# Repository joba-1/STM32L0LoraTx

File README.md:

# STM32L0LoraTx

Firmware and PCB for a device that sends data with a STM32L0/RFM95, battery or solar powered, to a [LoraGW ESP8266/RFM95 node](https://github.com/joba-1/LoraGw)

## Build

* Download and install STM32CubeIDE (as of now version 1.5.1)
* Import this repo
* Open .ioc file and select "Project/Generate Code" (should download needed "firmware" files for the chip from ST)
* Build Release or Debug

## Wiring

connect Gnd of all components

### STM32L011

Not checked without, but generally recommended to use a small ceramic (~10nF) and big electrolyt condensator (~10µF) between + and - near STM pins

* Look at the ioc file with CubeMX pinout view.
* Vdd _and_ Vdda to 1.8-3.3V
* Vss to Gnd
* Boot0 pulled to Gnd (~10k) to safely boot from flash
* STLink for flashing and debug: SWD, SWC, Gnd, NRst (also can provide Vdd via JP1 and STLink-Rx to L0-Tx for serial out)

### BME280

* SDA=MOSI, SDC=MISO, others should be obvious

### RFM95W

* Ant=~8cm wire (vary length and position to get best average RSSI as reported by LoraRx). 
* NSS=CS, others should be obvious

### Serial

Rx of a usb to serial converter sends at 115200. I use this command (serial port name ttyUSB_ser_red is defined in my /etc/udev/rules.d)
    pio device monitor -p /dev/ttyUSB_ser_red -b 115200

### LED

can be used without resistor. I use 1kOhm to save battery

## References

Good resource for STM32 is [Stefan Frings](http://stefanfrings.de/stm32/stm32l0.html)
He has links to reference, datasheet, errata and more. E.g.:

* [STM32L011 Datasheet](https://www.st.com/resource/en/datasheet/stm32l011d3.pdf)
* [STM32L011 Reference](https://www.st.com/resource/en/reference_manual/dm00108282-ultra-low-power-stm32l0x1-advanced-arm-based-32-bit-mcus-stmicroelectronics.pdf)
* [STM32L011 Errata](https://www.st.com/resource/en/errata_sheet/dm00237371-stm32l011x3-4-device-limitations-stmicroelectronics.pdf)
* [Power consumption](http://www.st.com/content/ccc/resource/technical/document/application_note/27/58/8e/81/79/fb/4f/ac/DM00108286.pdf/files/DM00108286.pdf/jcr:content/translations/en.DM00108286.pdf)

## Power Info Bits

* Examples for LL are here: STM32Cube/Repository/STM32Cube_FW_L0_V1.11.2/Projects/NUCLEO-L073RZ/Examples_LL/RTC/RTC_ExitStandbyWithWakeUpTimer
* Periodic wakeup timer is in Reference 22.4.6 (Periodic auto-wakeup)
* 1s to 18h periodic wakeup with ck_spre = 1s (see 22.4.3) and WUCKSEL [2:1] = 10
* Enable by WUTE bit in RTC_CR register
* Once setup it runs in normal and low power. 
* Sets WUTF flag in RTC_ISR if elapsed and reloads RTC_WUTR (timer counter). User resets WUTF
* Set WUTIE bit in RTC_CR to generate interrupt to wake up from low power modes
* System reset and Sleep, Stop, Standby have no influence on the WUT (wakeup timer)
* Save Lora frame counter in backup register: Reference 22.7.20 RTC backup registers (RTC_BKPxR)
* I couldnt make it work with LL lib, had to use big fat HAL for RCC and RTC. What is missing?

        LL_RTC_DisableWriteProtection(RTC);
        LL_RTC_WAKEUP_Disable(RTC);
        while( !LL_RTC_IsActiveFlag_WUTW(RTC) );
        LL_RTC_WAKEUP_SetClock(RTC, LL_RTC_WAKEUPCLOCK_CKSPRE);
        LL_RTC_WAKEUP_SetAutoReload(RTC, 3); // wake up every 3+1 s
        LL_RTC_EnableIT_WUT(RTC);
        LL_RTC_WAKEUP_Enable(RTC);
        LL_RTC_EnableWriteProtection(RTC);
        while( LL_RTC_IsActiveFlag_WUTW(RTC) );
        LL_RTC_ClearFlag_WUT(RTC);
        NVIC_ClearPendingIRQ(RTC_IRQn);

## Status

Working and sending LoRa packets to my LoraGW ESP8266 gateway (battery voltages and bme280 weather data)

Two devices operating with 2 AA 1.5V batteries (so far using 0.2-0.4 V per year, so >5 years between battery swaps is more than realistic).
They send battery voltage data from within a car trunc - not ideal for RF :) - to a nearby house with no signal problems.

One device runs "forever" with a 3.7 Lipo ~1.6Ah, a ~3x8 cm² 5V solar cell and a small solar charger board (reducing vcc out a bit with a diode). No capacity problems during winter.

## Todo

* Provide more sensor data (probably more ADC stuff and more generic)
* Move GPIO pins (CS, LED) to non-ADC pins to have them available for voltage measurements

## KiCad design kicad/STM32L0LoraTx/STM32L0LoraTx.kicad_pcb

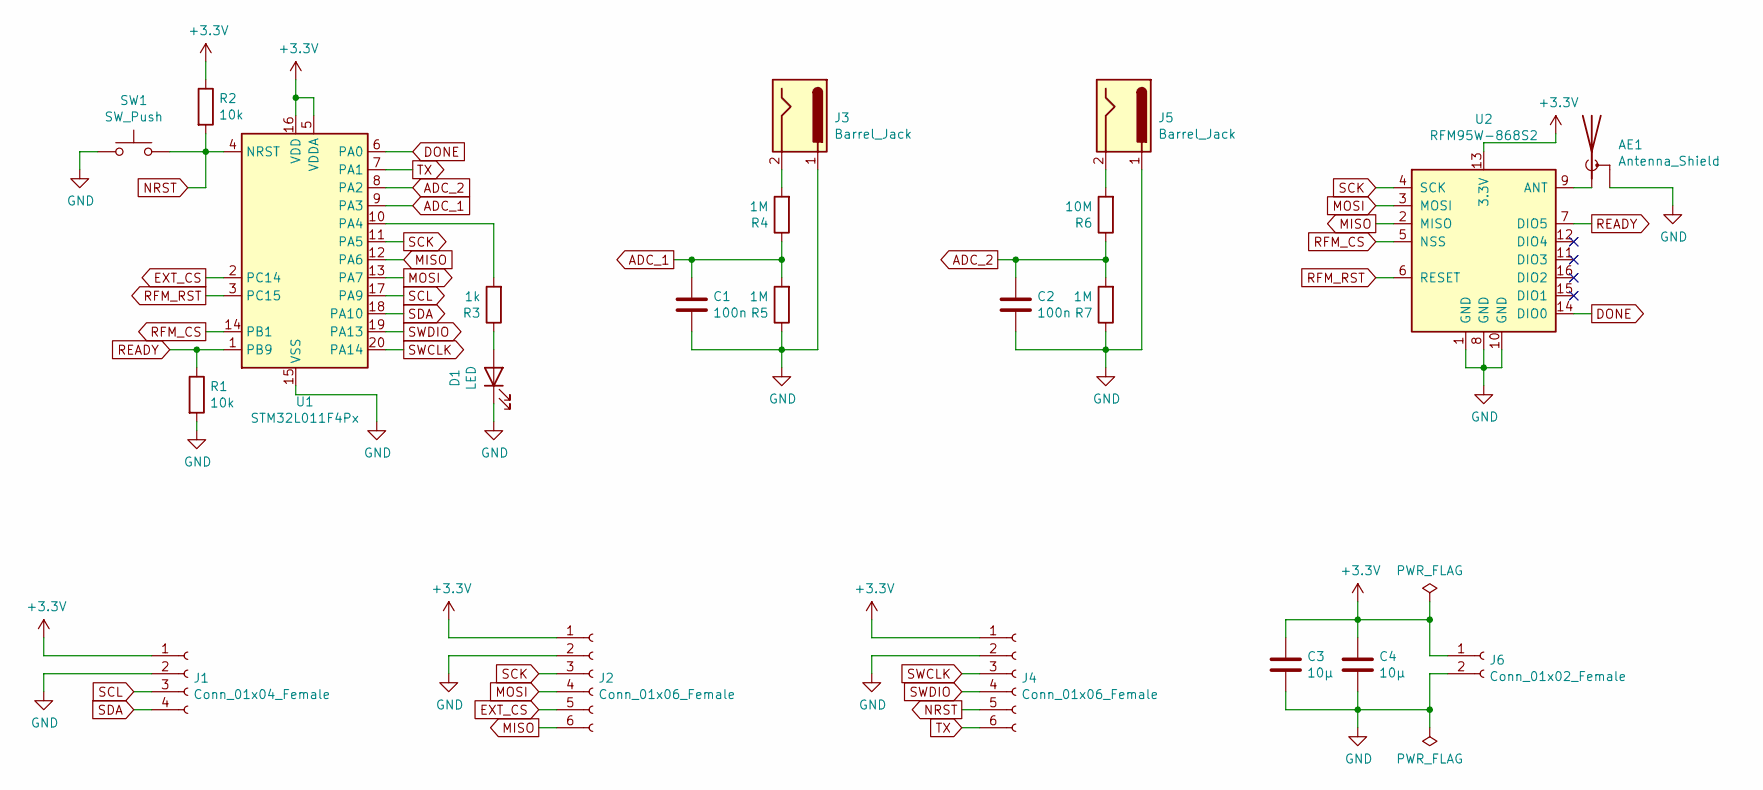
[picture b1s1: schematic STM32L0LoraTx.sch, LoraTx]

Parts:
AE1: Antenna_Shield; Molex_Microcoaxial_RF
C1, C2: 100n; C_0805_HandSoldering
C3, C4: 10µ; C_0805_HandSoldering
D1: LED; LED_0805_HandSoldering
J1: Conn_01x04_Female; JST_EH_B04B-EH-A_04x2.50mm_Straight
J2, J4: Conn_01x06_Female; JST_EH_B06B-EH-A_06x2.50mm_Straight
J3, J5: Barrel_Jack; TerminalBlock_Altech_AK300-2_P5.00mm
J6: Conn_01x02_Female; JST_EH_B02B-EH-A_02x2.50mm_Straight
R1, R2: 10k; R_0805_HandSoldering
R3: 1k; R_0805_HandSoldering
R4, R5, R7: 1M; R_0805_HandSoldering
R6: 10M; R_0805_HandSoldering
SW1: SW_Push; SW_PUSH_6mm_h5mm
U1: STM32L011F4Px; TSSOP-20_4.4x6.5mm_Pitch0.65mm
U2: RFM95W-868S2; Hopref_RFM9XW_SMD

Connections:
+3V3: C3.1, C4.1, J1.1, J2.1, J4.1, J6.1, R2.1, U1.5 (VDDA), U1.16 (VDD), U2.13 (3.3V)
ADC_1: C1.1, R4.1, R5.2, U1.9 (PA3)
ADC_2: C2.1, R6.1, R7.2, U1.8 (PA2)
DONE: U1.6 (PA0), U2.14 (DIO0)
EXT_CS: J2.5, U1.2 (PC14)
GND: AE1.2 (Shield), C1.2, C2.2, C3.2, C4.2, D1.1 (K), J1.2, J2.2, J3.1, J4.2, J5.1, J6.2, R1.2, R5.1, R7.1, SW1.1, U1.15 (VSS), U2.1 (GND), U2.8 (GND), U2.10 (GND); also elsewhere on the board
MISO: J2.6, U1.12 (PA6), U2.2 (MISO)
MOSI: J2.4, U1.13 (PA7), U2.3 (MOSI)
NRST: J4.5, R2.2, SW1.2, U1.4 (NRST); also elsewhere on the board
unnamed: AE1.1 (A), U2.9 (ANT)
unnamed: D1.2 (A), R3.1
unnamed: J3.2, R4.2
unnamed: J5.2, R6.2
unnamed: R3.2, U1.10 (PA4)
READY: R1.1, U1.1 (PB9), U2.7 (DIO5)
RFM_CS: U1.14 (PB1), U2.5 (NSS)
RFM_RST: U1.3 (PC15), U2.6 (RESET)
SCK: J2.3, U1.11 (PA5), U2.4 (SCK)
SCL: J1.3, U1.17 (PA9)
SDA: J1.4, U1.18 (PA10)
SWCLK: J4.3, U1.20 (PA14)
SWDIO: J4.4, U1.19 (PA13)
TX: J4.6, U1.7 (PA1)

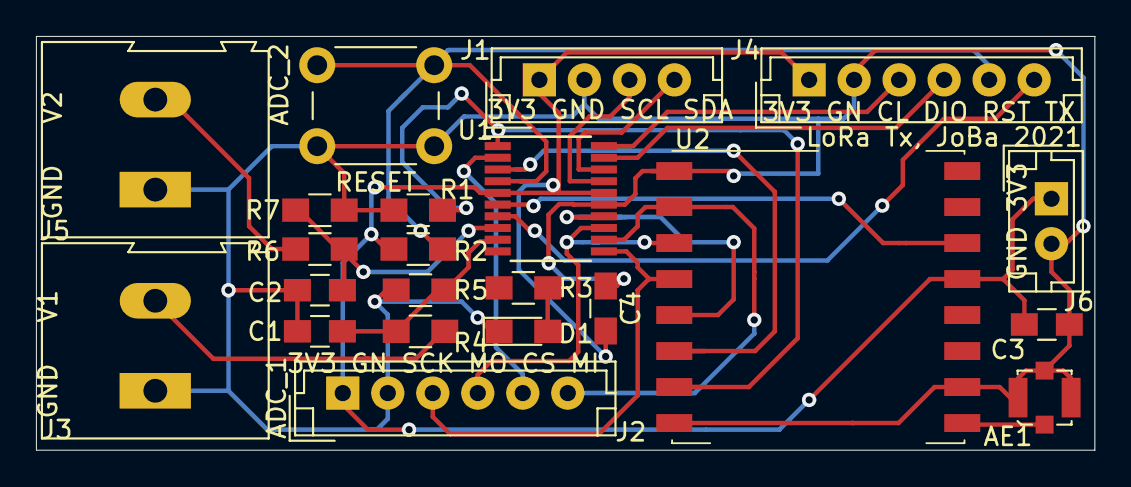
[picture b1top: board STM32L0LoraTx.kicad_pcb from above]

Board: 2 copper layers, 58.8 x 23.0 mm, 22 parts (0 on the bottom side), 23 nets.

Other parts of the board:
RESET: SW_Push; SW_PUSH_6mm_h5mm

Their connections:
GND: RESET.1; also elsewhere on the board
NRST: RESET.2; also elsewhere on the board

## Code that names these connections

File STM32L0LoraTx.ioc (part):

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PA0-CK_IN.GPIO_Label=RFM_D0
PA0-CK_IN.GPIOParameters=GPIO_Label
PA6.Mode=Full_Duplex_Master
PA7.Mode=Full_Duplex_Master
PA10.Mode=I2C
Mcu.UserName=STM32L011F4Px
PB9-BOOT0.GPIO_Label=RFM_D5
PA3.GPIOParameters=GPIO_Label
PC14-OSC32_IN.Signal=GPIO_Input
PA2.GPIOParameters=GPIO_Label
PC15-OSC32_OUT.GPIO_Label=RFM_NRST
PA3.Mode=IN3
PA13.Signal=SYS_SWDIO
PA9.Mode=I2C
PA9.Signal=I2C1_SCL
PC15-OSC32_OUT.Signal=GPIO_Output
PA1.Signal=LPUART1_TX
PA5.Signal=SPI1_SCK
RCC.HSE_VALUE=8000000
board=custom
PA0-CK_IN.Signal=GPIO_Input
PA1.Mode=Half_duplex(single_wire_mode)
PB9-BOOT0.GPIOParameters=GPIO_Label
PA14.Mode=Serial_Wire
PB1.GPIO_Label=RFM_CS
PA4.GPIOParameters=GPIO_Label
PA13.Mode=Serial_Wire
Mcu.Name=STM32L011F(3-4)Px
PC14-OSC32_IN.GPIOParameters=GPIO_Label
PA2.Signal=ADC_IN2
PA4.Signal=GPIO_Output
RCC.SYSCLKFreq_VALUE=1048000
Mcu.Package=TSSOP20
PA6.Signal=SPI1_MISO
PB1.Signal=GPIO_Output
PA2.GPIO_Label=ADC_ACCU
PA10.Signal=I2C1_SDA
PA14.Signal=SYS_SWCLK
PA2.Mode=IN2
PC14-OSC32_IN.GPIO_Label=EXT_CS
PC15-OSC32_OUT.GPIOParameters=GPIO_Label
PA4.GPIO_Label=LED
PA3.GPIO_Label=ADC_BAT
PA3.Signal=ADC_IN3
PB1.GPIOParameters=GPIO_Label
PA5.Mode=Full_Duplex_Master
PA7.Signal=SPI1_MOSI
PB9-BOOT0.Signal=GPIO_Input

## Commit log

2021-02-03 Lora Rx Tx working
2021-02-04 use external payload format
2021-02-04 payload with temperature
2021-02-04 version 1.2
2021-02-06 use temperature sensor
2021-02-06 ADC internal channel tests
2021-02-07 calibrated adc and allow neg voltage
2021-02-15 final voltage divider calibration
2021-02-15 add STM pin config
2021-02-22 add kicad
2021-03-04 save ioc
2022-05-31 pcb v4 board
2022-05-31 add bme280 support
